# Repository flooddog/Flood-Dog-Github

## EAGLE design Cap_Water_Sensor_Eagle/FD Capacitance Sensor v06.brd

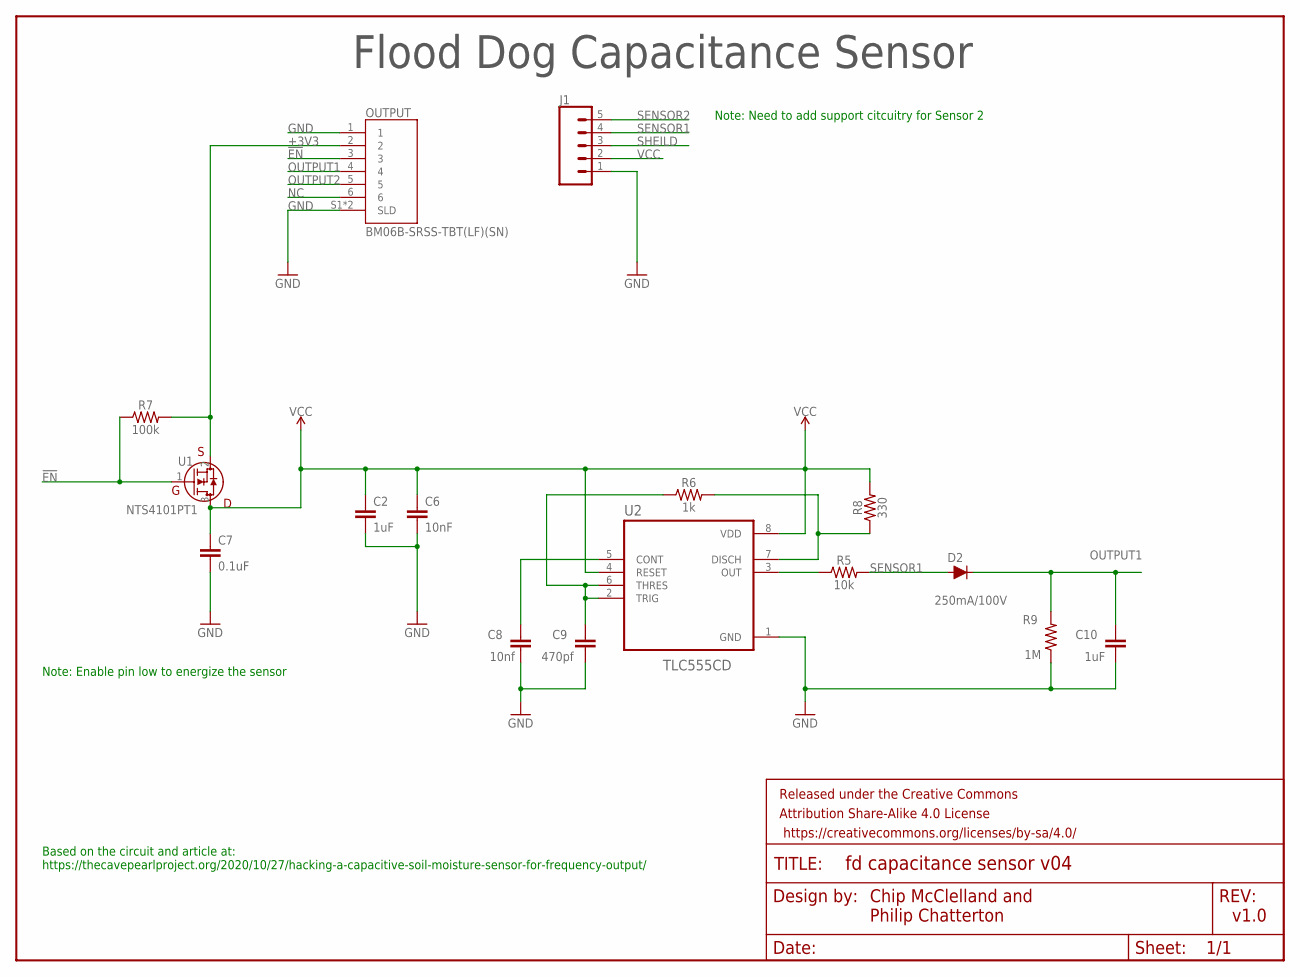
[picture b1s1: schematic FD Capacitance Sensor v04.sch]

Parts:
C2: 1uF; 0805@1
C6: 10nF; 0805@1
C7: 0.1uF; 0805@1
C8: 10nf; C0805
C9: 470pf; C0805
C10: 1uF; C0805
D2: 250mA/100V; SOD-323
FRAME1: FRAME-LETTERNO_PACKAGE; DUMMY
J1: CONN_05SCREW; SCREWTERMINAL-3.5MM-5
OUTPUT: BM06B-SRSS-TBT(LF)(SN); JST_BM06B-SRSS-TB(LF)(SN)
R5: 10k; 0805
R6: 1k; 0805
R7: 100k; 0805; MPN MF-RES-0805-100K
R8: 330; 0805
R9: 1M; 0805
U1: NTS4101PT1; SOT_101PT1_ONS
U2: TLC555CD; SOIC127P599X175-8N

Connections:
!EN: OUTPUT.3, R7.1, U1.1 (G)
+3V3: OUTPUT.2, R7.2, U1.2 (S)
GND: C2.2, C6.2, C7.2, C8.1, C9.1, C10.1, J1.1, OUTPUT.1, OUTPUT.S1 (SLD), OUTPUT.S2 (SLD), R9.1, U2.1 (GND)
unnamed: C8.2, U2.5 (CONT)
unnamed: R5.1, U2.3 (OUT)
unnamed: C9.2, R6.1, U2.2 (TRIG), U2.6 (THRES)
unnamed: R6.2, R8.1, U2.7 (DISCH)
NC: OUTPUT.6
OUTPUT1: C10.2, D2.C, OUTPUT.4, R9.2
OUTPUT2: OUTPUT.5
SENSOR1: D2.A, J1.4, R5.2
SENSOR2: J1.5
SHEILD: J1.3
VCC: C2.1, C6.1, C7.1, J1.2, R8.2, U1.3 (D), U2.4 (RESET), U2.8 (VDD)

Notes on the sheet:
Flood Dog Capacitance Sensor
v1.0
Chip McClelland and Philip Chatterton
Based on the circuit and article at: https://thecavepearlproject.org/2020/10/27/hacking-a-capacitive-soil-moisture-sensor-for-frequency-output/
Note: Need to add support citcuitry for Sensor 2
Note: Enable pin low to energize the sensor

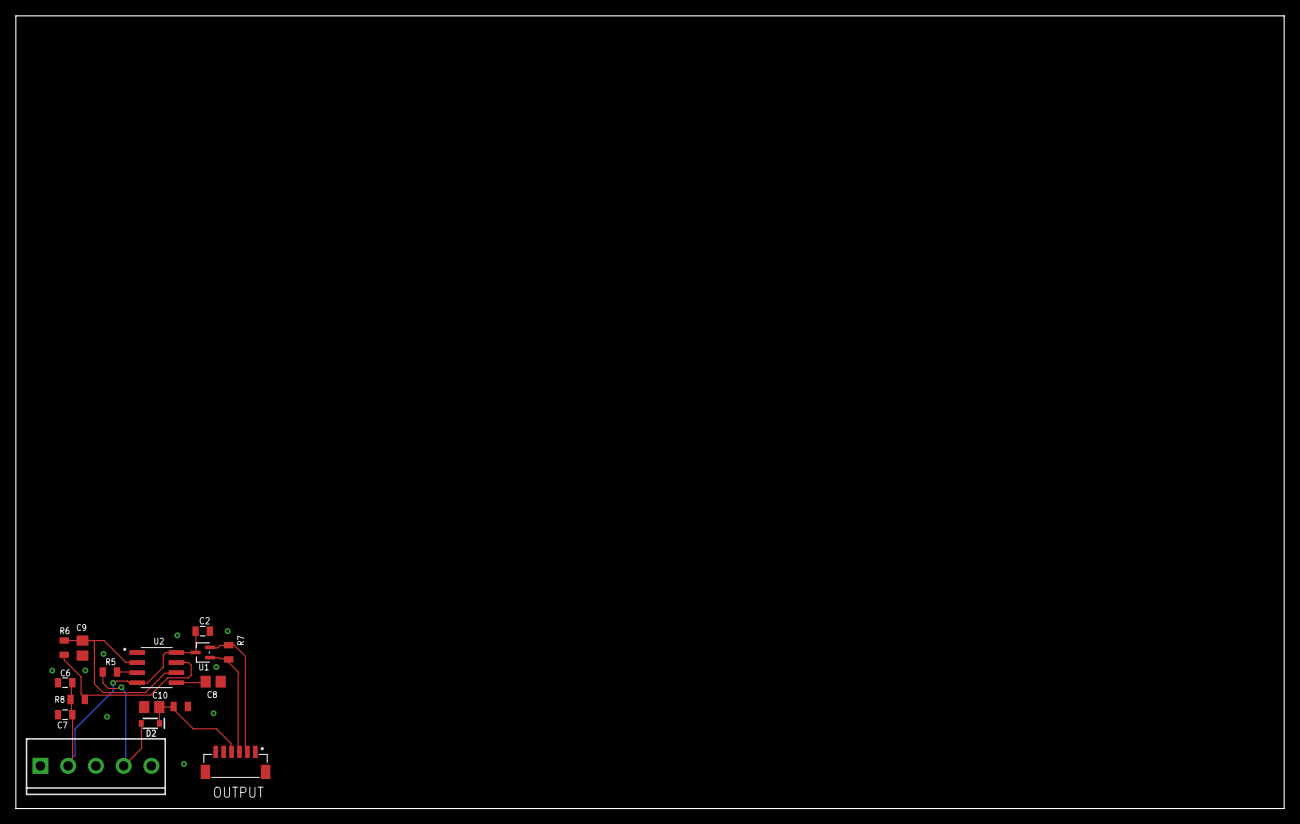
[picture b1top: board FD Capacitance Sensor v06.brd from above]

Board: 2 copper layers, 160.0 x 100.0 mm, 17 parts (0 on the bottom side), 10 nets.

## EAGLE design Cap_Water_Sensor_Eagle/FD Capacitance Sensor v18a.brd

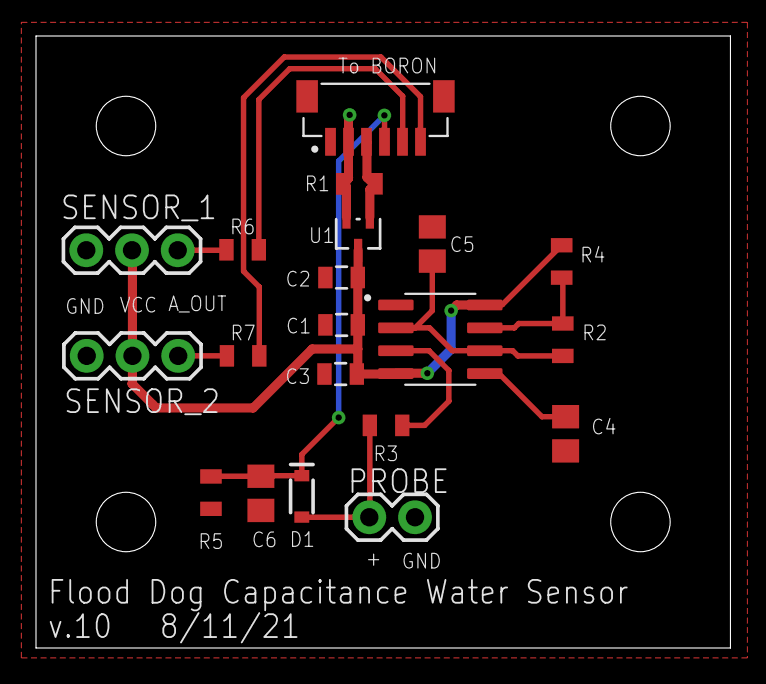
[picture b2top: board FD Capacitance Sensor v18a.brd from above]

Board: 2 copper layers, 38.6 x 34.0 mm, 25 parts (0 on the bottom side), 14 nets.

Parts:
C1: 0.1uF; 0805@1
C2: 1uF; 0805@1
C3: 10nF; 0805@1
C4: 10nf; C0805
C5: 470pf; C0805
C6: 1uF; C0805
D1: 250mA/100V; SOD-323
FRAME1: FRAME-LETTERNO_PACKAGE; DUMMY
J1: BM06B-SRSS-TBT(LF)(SN); JST_BM06B-SRSS-TB(LF)(SN)
PROBE: 1X02
R1: 100k; 0805
R2, R6, R7: 1k; 0805
R3: 10k; 0805
R4: 330; 0805
R5: 1M; 0805
SENSOR_1, SENSOR_2: 1X03
U1: NTS4101PT1; SOT_101PT1_ONS
U2: TLC555CD; SOIC127P599X175-8N
U$1, U$2, U$3, U$4: STAND-OFF

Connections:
!EN: J1.3, R1.1, U1.1
+3V3: J1.2, R1.2, U1.2
GND: C1.2, C2.2, C3.2, C4.1, C5.1, C6.1, J1.1, J1.S1, J1.S2, PROBE.2, R5.1, SENSOR_1.1, SENSOR_2.1, U2.1
unnamed: C4.2, U2.5
unnamed: R6.1, SENSOR_1.3
unnamed: R7.1, SENSOR_2.3
unnamed: R3.1, U2.3
unnamed: C5.2, R2.1, U2.2, U2.6
unnamed: R2.2, R4.1, U2.7
PROBE+: D1.A, PROBE.1, R3.2
SIGNAL_A0: C6.2, D1.C, J1.4, R5.2
SIGNAL_A1: J1.5, R6.2
SIGNAL_A2: J1.6, R7.2
VCC: C1.1, C2.1, C3.1, R4.2, SENSOR_1.2, SENSOR_2.2, U1.3, U2.4, U2.8

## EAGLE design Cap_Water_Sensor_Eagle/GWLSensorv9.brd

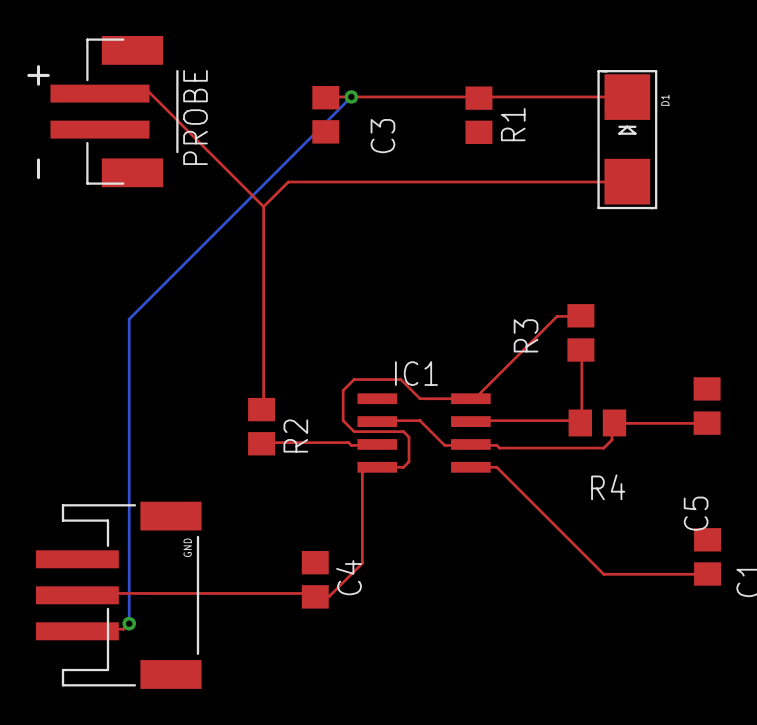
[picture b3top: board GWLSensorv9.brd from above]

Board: 2 copper layers, 12 parts (0 on the bottom side), 8 nets.

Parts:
C1: 10nf; C0805
C3: 1n; C0805
C4: 100nf; C0805
C5: 470pf; C0805
D1: SMADIODE
GND: JSTPH3
IC1: LM555D; SO08
PROBE: JST-PH-2-SMT
R1: 1M; R0805
R2: 10K; R0805
R3: 330; R0805
R4: 1K6; R0805

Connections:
GND: C1.1, C3.2, C4.1, C5.2, GND.1, IC1.1, PROBE.2, R1.2
unnamed: IC1.7, R3.2, R4.1
unnamed: C5.1, IC1.2, IC1.6, R4.2
unnamed: C1.2, IC1.5
unnamed: D1.A, PROBE.1, R2.1
unnamed: IC1.3, R2.2
SIGNAL: C3.1, D1.C, GND.3, R1.1
VCC: C4.2, GND.2, IC1.4, IC1.8, R3.1

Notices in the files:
parts and their libraries:
SparkFun-Connectors: Licensing: Creative Commons ShareAlike 4.0 International - https://creativecommons.org/licenses/by-sa/4.0
SparkFun-Aesthetics: Released under the Creative Commons Attribution Share-Alike 4.0 License
SparkFun-Aesthetics: https://creativecommons.org/licenses/by-sa/4.0
